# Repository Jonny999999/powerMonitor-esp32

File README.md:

# ESP32 PV Power Monitoring System

This project documents a system for monitoring photovoltaic (PV) power production and household power consumption using **ESP32** and **PZEM-004T** / **PZEM-016** power sensors, with data published over **MQTT**.

Included in this repo:

- Firmware for several ESP32 individually configured breakout boards, built with ESP-IDF 5.3
- Python utility for configuring PZEM modules over USB serial
- Hardware project for a custom UART ↔ RS485 interface board (KiCad) for a simple stripboard

---

## Dashboard Demo

The following screenshots show the resulting dashboard created using Node-RED where the sensor data is received via MQTT and stored in a database.
The charts visualize all sensor values across multiple inverters and locations.

### Live Chart View (Total sum, Active power, Current)

---

### Live Chart View (Power factor, Voltage, Frequency)

---

## Hardware Setup

Below are a few example photos of the current wiring and hardware setup.

### 3x PZEM-003T measuring total consumption (main distribution board)

Used for measuring total consumption of the entire building. One module for each phase (L1, L2, L3).

---

### Single PZEM-004T (inverter distribution box)

Each module is wired to one phase of a single inverter output.

---

### 2× PZEM-016 via RS485 (distribution box Remote inverters)

PZEM-016 modules connected via a shared RS485 bus and assigned separate Modbus addresses.  
On the other side of a ~30 m 5×1.5 mm² power cable, an ESP32 with a custom RS485-to-UART PCB receives the data and publishes it via MQTT.

---

## UART ↔ RS485 Interface (Custom PCB)

To interface the ESP32 with RS485-based PZEM-016 sensors, a small PCB based on the **MAX3485** transceiver was created.

- KiCad Project: [`hardware/UART-RS485_interface-board/`](hardware/UART-RS485_interface-board/)
- Schematic PDF: [`schematic.pdf`](hardware/UART-RS485_interface-board/export/schematic.pdf)

### Photo while testing

---

## Firmware (ESP32)

Firmware for reading multiple PZEM modules and publishing the values via MQTT.  
Tested with ESP-IDF 5.3.

### Features

- Supports **PZEM-004T v3** (TTL UART) and **PZEM-016** (RS485)
- Configurable (per module):
  - Sensor address
  - GPIO pins (TX, RX, RTS)
  - MQTT topic prefix
  - Publish interval
  - Sensor type (TTL / RS485)
- Reads and publishes:
  - Voltage
  - Current
  - Power
  - Energy
  - Frequency
  - Power factor

### Build and Flash
Make sure ESP-IDF 5.3 is sourced:

```bash
. /opt/esp-idf-v5.3/v5.3/esp-idf/export.sh
cd esp32_power-monitor
idf.py build flash monitor
```

---

## Python Utility (`power-meter.py`)

Utility script for directly configuring and reading PZEM modules using a USB-to-Serial adapter.

### Functions

- Set or change Modbus address
- Reset energy counter
- Read live values

### Requirements

```bash
pip install pyserial
```

### Usage
1. Connect **RX/TX** of the FTDI adapter to the **TX/RX** of the PZEM module.
2. Plug the adapter into your PC.
3. Edit `pzem_tool.py`:
   - Set the correct serial port and slave ID
   - Uncomment the function you want to run (read, configure, reset)

Then run the script:

```bash
python3 pzem_tool.py
```

---

## Repository Structure

```
firmware/    # Several ESP-IDF projects for all instances running
hardware/UART-RS485_interface-board/   # KiCad project for interface PCB
doc/images/                            # photos and documentation
```

---

## Notes

- PZEM modules must be addressed and wired correctly (especially for RS485).
- Each PZEM sensor input should be fused and installed safely. Here i used a 200 mA 5x20 mm fuse for each module in the gray WAGO fuse holders for DIN rail.
- Wi-Fi credentials are configured via `main/credentials.h` which is not tracked in the repo.

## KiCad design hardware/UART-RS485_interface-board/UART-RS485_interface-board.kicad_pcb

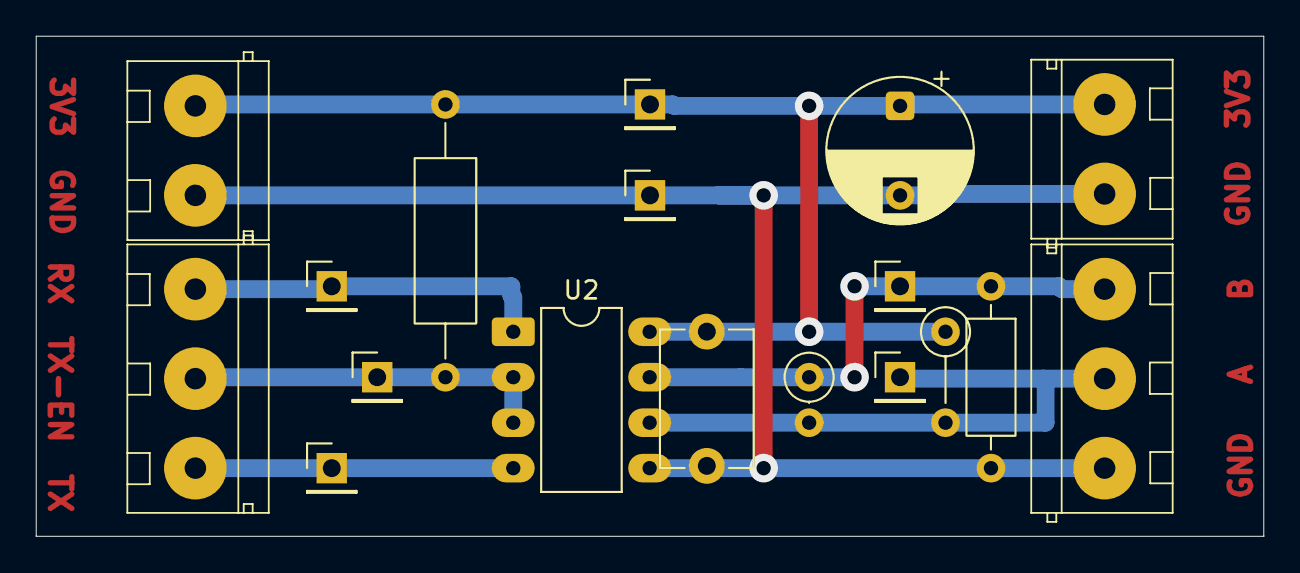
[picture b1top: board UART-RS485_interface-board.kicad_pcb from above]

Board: 4 copper layers, 68.6 x 27.9 mm, 18 parts (0 on the bottom side), 7 nets.

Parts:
C1: 100n; C_Disc_D7.5mm_W5.0mm_P7.50mm
C2: 10uf; CP_Radial_D8.0mm_P5.00mm
J1: [TX, DIR, RX] UART (ESP32); ScrewTerminal_P5mm_3Pin_FP15x8
J2, J3: GND, 3v3; ScrewTerminal_P5mm_2Pin_FP10x8
J8: [GND, A, B] RS485 (Sensor); ScrewTerminal_P5mm_3Pin_FP15x8
R17: 10k; R_Axial_DIN0309_L9.0mm_D3.2mm_P15.24mm_Horizontal
R35: 3k3; R_Axial_DIN0207_L6.3mm_D2.5mm_P5.08mm_Vertical
R36: 120; R_Axial_DIN0207_L6.3mm_D2.5mm_P2.54mm_Vertical
R37: 3k3; R_Axial_DIN0207_L6.3mm_D2.5mm_P10.16mm_Horizontal
TP1: TX; PinHeader_1x01_P2.54mm_Vertical
TP2: RX; PinHeader_1x01_P2.54mm_Vertical
TP3: RS-A; PinHeader_1x01_P2.54mm_Vertical
TP4: DIR; PinHeader_1x01_P2.54mm_Vertical
TP5: RS-B; PinHeader_1x01_P2.54mm_Vertical
TP6: 3v3; PinHeader_1x01_P2.54mm_Vertical
TP7: gnd; PinHeader_1x01_P2.54mm_Vertical
U2: MAX3485; DIP-8_W7.62mm_LongPads

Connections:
+3V3: C1.1, C2.1, J2.1, J3.2, R17.1, R35.1, TP6.1, U2.8 (VCC)
/RS485-A: J8.2, R35.2, R36.2, TP3.1, U2.6 (A)
/RS485-B: J8.3, R36.1, R37.1, TP5.1, U2.7 (B)
/RS485_DIR: J1.2, R17.2, TP4.1, U2.2 (~RE), U2.3 (DE)
/RS485_RX: J1.1, TP2.1, U2.1 (RO)
/RS485_TX: J1.3, TP1.1, U2.4 (DI)
GND: C1.2, C2.2, J2.2, J3.1, J8.1, R37.2, TP7.1, U2.5 (GND)

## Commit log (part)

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2025-05-01 Init - python script for reading sensor works
2025-05-01 Add functions for setting slave-addr + resetting power
2025-05-03 Copy mqtt demo esp-idf project
2025-05-03 Add library for pzem004t - readout works (example)
2025-05-03 Add custom task to read multiple sensors, Adjust pzem init func to deinit UART first
2025-05-03 Add wifi+mqtt init, publish all data, Add actual 4 sensors
2025-05-24 Add wifi reconnect, Retry earlier when read failed
2025-05-24 Add Readme and photos
2025-05-25 Change project structure, Outsource common code (to support multiple boards)
2025-05-25 Add kicad Project for UART-RS485_interface-board
2025-05-29 UART-RS485 Stripboard: Adjust as actually soldered, fixes, add exports
2025-05-29 Add support for RS485 modules
2025-05-29 Create esp-idf project 'neue-schupfe' (copy project 'schupfe')
2025-05-29 Adjust config (2x RS485 Sensors, IP, test-interval)
2025-05-30 Create esp-idf project 'hobelboden' (copy project 'neue-schupfe')
2025-05-30 Adjust config (1x TTL sensor, IP)
2025-05-30 Add mode for resetting energy to powermon_task, Set publish interval to 60s (all boards)
2025-05-31 Fix energy reset func in pzem library (untested)
2025-05-31 Fix RESET_ENERGY mode in pMonTask (also reset all sensors)
2025-05-31 Create esp-idf project 'esp32_hak', Configure 3 sensors, 30s interval
2025-06-12 Add photos of wiring and board
2025-06-12 Update Readme: Add photos, Add pcb-project
2026-06-21 Instance schupfe config: Disable all removed inverters
